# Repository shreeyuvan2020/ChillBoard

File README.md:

# The Chillboard
 ## The perfect ergonomic keyboard for chilling
 ## Features
 - Uses Xiao NRF52840 for low power usage and BLE capabilities
 - Wireless design with a 2000 mAh battery and BLE
 - CPG1350 hotswap sockets for customizabilty
 - Low profile choc switches for portability
 - Neopixel backlighting for layer switching
 - OLED panel for battery percentage
 - Tray mounted for easy assembly
 - Rotary encoder for volume control
 - PIR sensor for energy conservation
 - Ortholinear layout with a thumb cluster to reduce strain
## Reasons I built this
 - Right now, I type on a laptop keyboard and am scared that I might get carpal tunnel.
 - The switches on my other keyboard are very loud, and are not the best for me. Hotswap sockets let me customize the feel.
 - The keyboard doesn't have backlighting.
## Schematic
 For the schematic, I used hierarchial sheets to organize everything. There are 2 hierarchial sheets for each side of the pcb, and a hierarchial sheet in each one of those for the large neopixel matrix. 

 - 
 - 
 - 
## PCB
 I designed the PCB with mousebites to make the split keyboard easy to manufacture. I thought of making a reversible PCB at first, but it would be very difficult with an OLED. 
  ### Left side of the PCB 
  
  ### Full PCB
  
  ### 3D View
  
## CAD
 I designed the CAD with ease of assembly in mind. That is why I designed it with no tolerances, so that it could completely friction fit(I added screw holes for the worst case). I decided to print it with an extra fine setting on my Bambu Lab A1 Mini 3D printer, and it turned out great. 
 ### Bottom Case
 
 ### Top Plate
 
 ### Full Assembly
 
 ### Pictures of it Assembled

## My Zine

Zine is at zine.pdf too
## Assembly Instructions
 - First, obviously fabricate the PCB and solder everything.
 - Next is printing the plate and case.
 - Print with very fine settings as it friction fits, I printed with 0.08 mm High Quality @BBL on my Bambu Labs A1 Mini.
 - Be careful when removing the plate and bottom from the print bed as it could break
 - Obviously print two of each, two plates and two bottom cases
 - Then, go into the Firmware folder, open the submodule, and open Github Actions
 - Click the latest build and download the firmware artifact.
 - Then, plug in a USB cable into the Xiao and hit the reset button 2 times
 - A drive should show up, drop the first file that says settings-reset etc.
 - The drive should disappear, wait about 5 seconds and then do the same thing again
 - Then drop the file that starts with custom21
 - Now disconnect the cable, and it should show up as a BLE device
 - Connect to it then put the PCB into the bottom case
 - Then put the plate on top of it and place the keycaps on top of that to secure it.
 - You're good to go!
## Credits
 This project is inspired by the Corneucopia project by @DynamicWhiteHat.
 It used Autodesk Fusion for CAD, Kicad 10 for the PCB, and is sponsored by Hack Club Fallout! Thanks to Hack Club for sponsoring this!

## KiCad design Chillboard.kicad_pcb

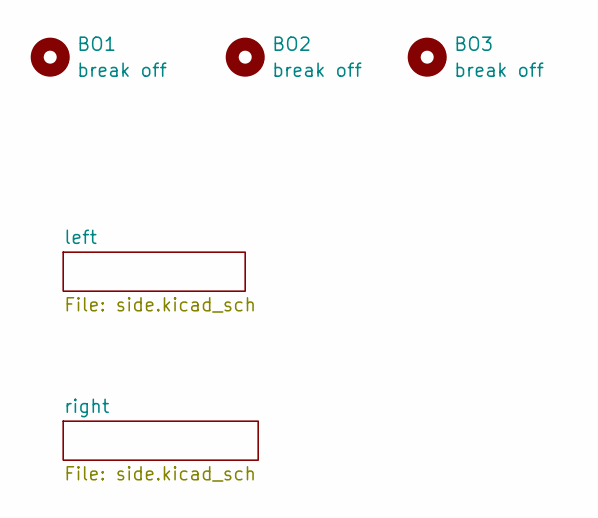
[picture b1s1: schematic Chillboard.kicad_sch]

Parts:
BO1, BO2, BO3: break off; mouse-bite-3mm-slot

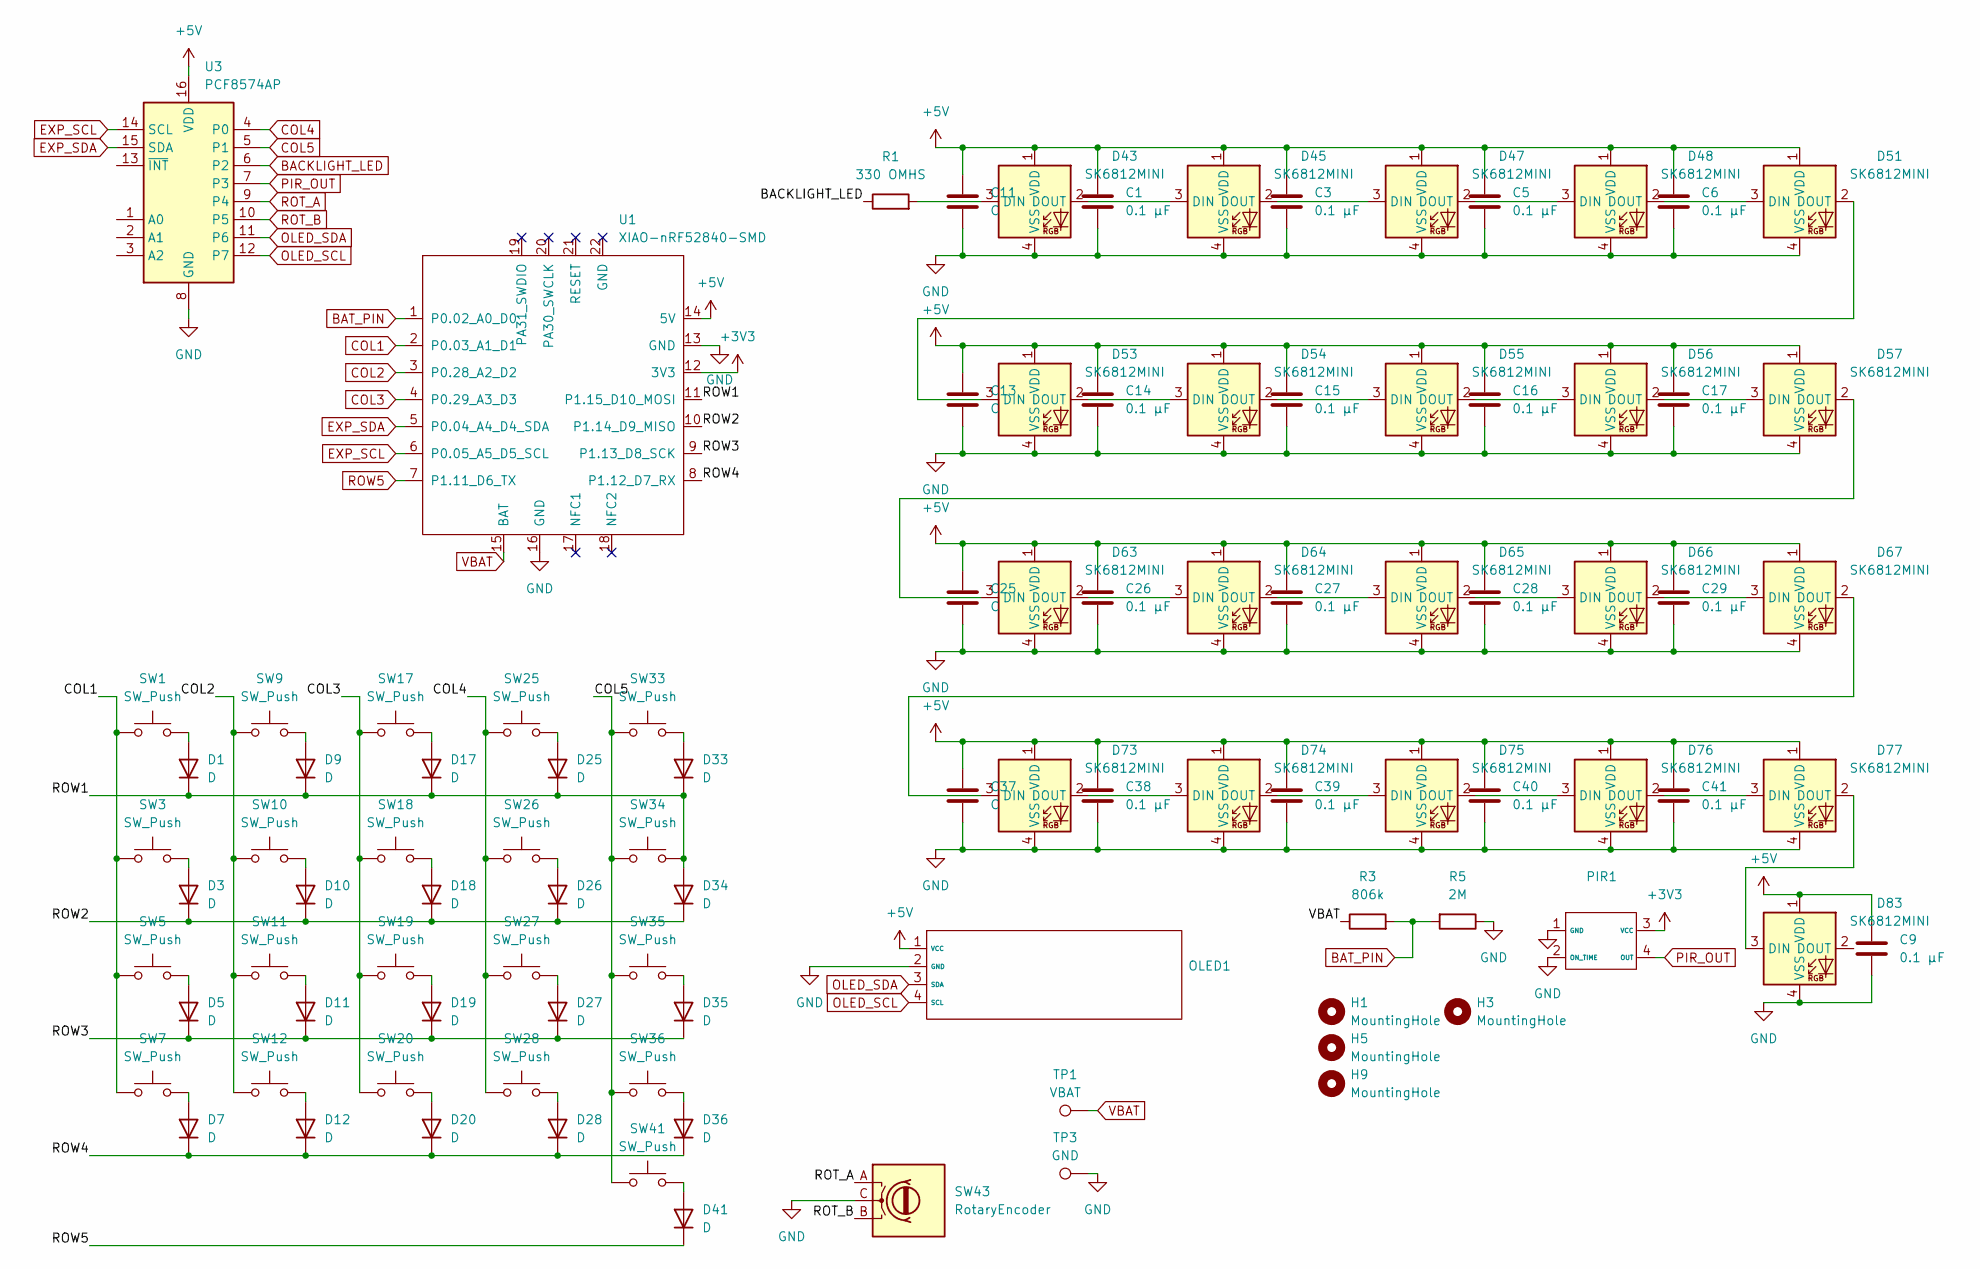
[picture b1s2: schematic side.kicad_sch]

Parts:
C1, C3, C5, C6, C9, C14, C15, C16, C17, C26, C27, C28, C29, C38, C39, C40, C41: 0.1 μF; C_0805_2012Metric
C11, C13, C25, C37: C; C_0805_2012Metric
D1, D3, D5, D7, D9, D10, D11, D12, D17, D18, D19, D20, D25, D26, D27, D28, D33, D34, D35, D36, D41: D; D_SOD-123
D43, D45, D47, D48, D51, D53, D54, D55, D56, D57, D63, D64, D65, D66, D67, D73, D74, D75, D76, D77, D83: SK6812MINI; LED_6028R
H1, H3, H5, H9: MountingHole; MountingHole_2.1mm
OLED1: SSD1306-0.91-OLED-4pin-128x32
PIR1: BS412
R1: 330 OMHS; R_Axial_DIN0207_L6.3mm_D2.5mm_P10.16mm_Horizontal
R3: 806k; R_Axial_DIN0207_L6.3mm_D2.5mm_P10.16mm_Horizontal
R5: 2M; R_Axial_DIN0207_L6.3mm_D2.5mm_P10.16mm_Horizontal
SW1, SW3, SW5, SW9, SW10, SW11, SW12, SW17, SW18, SW19, SW20, SW25, SW26, SW27, SW28, SW33, SW34, SW35, SW36, SW41: SW_Push; SW_choc_v1_HS_CPG135001S30_1u
SW7: SW_Push; SW_choc_v1_HS_CPG135001S30_1.5u
SW43: RotaryEncoder; RotaryEncoder_Alps_EC11E_Vertical_H20mm
TP1: VBAT; TestPoint_Pad_D2.0mm
TP3: GND; TestPoint_Pad_D2.0mm
U1: XIAO-nRF52840-SMD; modified-XIAO-nRF52840-SMD
U3: PCF8574AP; DIP-16_W7.62mm

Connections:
+3V3: PIR1.3 (VCC), U1.12 (3V3); also elsewhere on the board
+5V: C1.1, C3.1, C5.1, C6.1, C9.1, C11.1, C13.1, C14.1, C15.1, C16.1, C17.1, C25.1, C26.1, C27.1, C28.1, C29.1, C37.1, C38.1, C39.1, C40.1, C41.1, D43.1 (VDD), D45.1 (VDD), D47.1 (VDD), D48.1 (VDD), D51.1 (VDD), D53.1 (VDD), D54.1 (VDD), D55.1 (VDD), D56.1 (VDD), D57.1 (VDD), D63.1 (VDD), D64.1 (VDD), D65.1 (VDD), D66.1 (VDD), D67.1 (VDD), D73.1 (VDD), D74.1 (VDD), D75.1 (VDD), D76.1 (VDD), D77.1 (VDD), D83.1 (VDD), OLED1.1 (VCC), U1.14 (5V), U3.16 (VDD); also elsewhere on the board
/left/ROW1: D1.1 (K), D9.1 (K), D17.1 (K), D25.1 (K), D33.1 (K), D34.2 (A), SW34.2, U1.11 (P1.15_D10_MOSI)
/left/ROW2: D3.1 (K), D10.1 (K), D18.1 (K), D26.1 (K), D34.1 (K), U1.10 (P1.14_D9_MISO)
/left/ROW3: D5.1 (K), D11.1 (K), D19.1 (K), D27.1 (K), D35.1 (K), U1.9 (P1.13_D8_SCK)
/left/ROW4: D7.1 (K), D12.1 (K), D20.1 (K), D28.1 (K), D36.1 (K), U1.8 (P1.12_D7_RX)
BACKLIGHT_LED: R1.1, U3.6 (P2); also elsewhere on the board
BAT_PIN: R3.2, R5.2, U1.1 (P0.02_A0_D0); also elsewhere on the board
COL1: SW1.1, SW3.1, SW5.1, SW7.1, U1.2 (P0.03_A1_D1); also elsewhere on the board
COL2: SW9.1, SW10.1, SW11.1, SW12.1, U1.3 (P0.28_A2_D2); also elsewhere on the board
COL3: SW17.1, SW18.1, SW19.1, SW20.1, U1.4 (P0.29_A3_D3); also elsewhere on the board
COL4: SW25.1, SW26.1, SW27.1, SW28.1, U3.4 (P0); also elsewhere on the board
COL5: SW33.1, SW34.1, SW35.1, SW36.1, SW41.1, U3.5 (P1); also elsewhere on the board
EXP_SCL: U1.6 (P0.05_A5_D5_SCL), U3.14 (SCL); also elsewhere on the board
EXP_SDA: U1.5 (P0.04_A4_D4_SDA), U3.15 (SDA); also elsewhere on the board
GND: C1.2, C3.2, C5.2, C6.2, C9.2, C11.2, C13.2, C14.2, C15.2, C16.2, C17.2, C25.2, C26.2, C27.2, C28.2, C29.2, C37.2, C38.2, C39.2, C40.2, C41.2, D43.4 (VSS), D45.4 (VSS), D47.4 (VSS), D48.4 (VSS), D51.4 (VSS), D53.4 (VSS), D54.4 (VSS), D55.4 (VSS), D56.4 (VSS), D57.4 (VSS), D63.4 (VSS), D64.4 (VSS), D65.4 (VSS), D66.4 (VSS), D67.4 (VSS), D73.4 (VSS), D74.4 (VSS), D75.4 (VSS), D76.4 (VSS), D77.4 (VSS), D83.4 (VSS), OLED1.2 (GND), PIR1.1 (GND), PIR1.2 (ON_TIME), R5.1, SW43.C, TP3.1 (1_1), U1.13 (GND), U1.16 (GND), U3.8 (GND); also elsewhere on the board
unnamed: D1.2 (A), SW1.2
unnamed: D3.2 (A), SW3.2
unnamed: D5.2 (A), SW5.2
unnamed: D7.2 (A), SW7.2
unnamed: D9.2 (A), SW9.2
unnamed: D10.2 (A), SW10.2
unnamed: D11.2 (A), SW11.2
unnamed: D12.2 (A), SW12.2
unnamed: D17.2 (A), SW17.2
unnamed: D18.2 (A), SW18.2
unnamed: D19.2 (A), SW19.2
unnamed: D20.2 (A), SW20.2
unnamed: D25.2 (A), SW25.2
unnamed: D26.2 (A), SW26.2
unnamed: D27.2 (A), SW27.2
unnamed: D28.2 (A), SW28.2
unnamed: D33.2 (A), SW33.2
unnamed: D35.2 (A), SW35.2
unnamed: D36.2 (A), SW36.2
unnamed: D41.2 (A), SW41.2
unnamed: D43.3 (DIN), R1.2
unnamed: D43.2 (DOUT), D45.3 (DIN)
unnamed: D45.2 (DOUT), D47.3 (DIN)
unnamed: D47.2 (DOUT), D48.3 (DIN)
unnamed: D48.2 (DOUT), D51.3 (DIN)
unnamed: D51.2 (DOUT), D53.3 (DIN)
unnamed: D53.2 (DOUT), D54.3 (DIN)
unnamed: D54.2 (DOUT), D55.3 (DIN)
unnamed: D55.2 (DOUT), D56.3 (DIN)
unnamed: D56.2 (DOUT), D57.3 (DIN)
unnamed: D57.2 (DOUT), D63.3 (DIN)
unnamed: D63.2 (DOUT), D64.3 (DIN)
unnamed: D64.2 (DOUT), D65.3 (DIN)
unnamed: D65.2 (DOUT), D66.3 (DIN)
unnamed: D66.2 (DOUT), D67.3 (DIN)
unnamed: D67.2 (DOUT), D73.3 (DIN)
unnamed: D73.2 (DOUT), D74.3 (DIN)
unnamed: D74.2 (DOUT), D75.3 (DIN)
unnamed: D75.2 (DOUT), D76.3 (DIN)
unnamed: D76.2 (DOUT), D77.3 (DIN)
unnamed: D77.2 (DOUT), D83.3 (DIN)
OLED_SCL: OLED1.4 (SCL), U3.12 (P7); also elsewhere on the board
OLED_SDA: OLED1.3 (SDA), U3.11 (P6); also elsewhere on the board
PIR_OUT: PIR1.4 (OUT), U3.7 (P3); also elsewhere on the board
ROT_A: SW43.A, U3.9 (P4); also elsewhere on the board
ROT_B: SW43.B, U3.10 (P5); also elsewhere on the board
ROW5: D41.1 (K), U1.7 (P1.11_D6_TX); also elsewhere on the board
VBAT: R3.1, TP1.1 (1_1), U1.15 (BAT); also elsewhere on the board

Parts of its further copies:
C2, C4, C7, C8, C10, C20, C21, C22, C23, C32, C33, C34, C35, C44, C45, C46, C47: 0.1 μF; C_0805_2012Metric
C12, C19, C31, C43: C; C_0805_2012Metric
D2, D4, D6, D8, D13, D14, D15, D16, D21, D22, D23, D24, D29, D30, D31, D32, D37, D38, D39, D40, D42: D; D_SOD-123
D44, D46, D49, D50, D52, D58, D59, D60, D61, D62, D68, D69, D70, D71, D72, D78, D79, D80, D81, D82, D84: SK6812MINI; LED_6028R
H2, H4, H7, H11: MountingHole; MountingHole_2.1mm
R2: 330 OMHS; R_Axial_DIN0207_L6.3mm_D2.5mm_P10.16mm_Horizontal
R4: 806k; R_Axial_DIN0207_L6.3mm_D2.5mm_P10.16mm_Horizontal
R6: 2M; R_Axial_DIN0207_L6.3mm_D2.5mm_P10.16mm_Horizontal
SW2, SW4, SW6, SW13, SW14, SW15, SW16, SW21, SW22, SW23, SW24, SW29, SW30, SW31, SW32, SW37, SW38, SW39, SW40, SW42: SW_Push; SW_choc_v1_HS_CPG135001S30_1u
SW8: SW_Push; SW_choc_v1_HS_CPG135001S30_1.5u
SW44: RotaryEncoder; RotaryEncoder_Alps_EC11E_Vertical_H20mm
TP2: VBAT; TestPoint_Pad_D2.0mm
TP4: GND; TestPoint_Pad_D2.0mm
U2: XIAO-nRF52840-SMD; modified-XIAO-nRF52840-SMD
U4: PCF8574AP; DIP-16_W7.62mm

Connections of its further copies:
+3V3: U2.12 (3V3); also elsewhere on the board
+5V: C2.1, C4.1, C7.1, C8.1, C10.1, C12.1, C19.1, C20.1, C21.1, C22.1, C23.1, C31.1, C32.1, C33.1, C34.1, C35.1, C43.1, C44.1, C45.1, C46.1, C47.1, D44.1 (VDD), D46.1 (VDD), D49.1 (VDD), D50.1 (VDD), D52.1 (VDD), D58.1 (VDD), D59.1 (VDD), D60.1 (VDD), D61.1 (VDD), D62.1 (VDD), D68.1 (VDD), D69.1 (VDD), D70.1 (VDD), D71.1 (VDD), D72.1 (VDD), D78.1 (VDD), D79.1 (VDD), D80.1 (VDD), D81.1 (VDD), D82.1 (VDD), D84.1 (VDD), U2.14 (5V), U4.16 (VDD); also elsewhere on the board
/right/ROW1: D2.1 (K), D13.1 (K), D21.1 (K), D29.1 (K), D37.1 (K), D38.2 (A), SW38.2, U2.11 (P1.15_D10_MOSI)
/right/ROW2: D4.1 (K), D14.1 (K), D22.1 (K), D30.1 (K), D38.1 (K), U2.10 (P1.14_D9_MISO)
/right/ROW3: D6.1 (K), D15.1 (K), D23.1 (K), D31.1 (K), D39.1 (K), U2.9 (P1.13_D8_SCK)
/right/ROW4: D8.1 (K), D16.1 (K), D24.1 (K), D32.1 (K), D40.1 (K), U2.8 (P1.12_D7_RX)
BACKLIGHT_LED: R2.1, U4.6 (P2); also elsewhere on the board
BAT_PIN: R4.2, R6.2, U2.1 (P0.02_A0_D0); also elsewhere on the board
COL1: SW2.1, SW4.1, SW6.1, SW8.1, U2.2 (P0.03_A1_D1); also elsewhere on the board
COL2: SW13.1, SW14.1, SW15.1, SW16.1, U2.3 (P0.28_A2_D2); also elsewhere on the board
COL3: SW21.1, SW22.1, SW23.1, SW24.1, U2.4 (P0.29_A3_D3); also elsewhere on the board
COL4: SW29.1, SW30.1, SW31.1, SW32.1, U4.4 (P0); also elsewhere on the board
COL5: SW37.1, SW38.1, SW39.1, SW40.1, SW42.1, U4.5 (P1); also elsewhere on the board
EXP_SCL: U2.6 (P0.05_A5_D5_SCL), U4.14 (SCL); also elsewhere on the board
EXP_SDA: U2.5 (P0.04_A4_D4_SDA), U4.15 (SDA); also elsewhere on the board
GND: C2.2, C4.2, C7.2, C8.2, C10.2, C12.2, C19.2, C20.2, C21.2, C22.2, C23.2, C31.2, C32.2, C33.2, C34.2, C35.2, C43.2, C44.2, C45.2, C46.2, C47.2, D44.4 (VSS), D46.4 (VSS), D49.4 (VSS), D50.4 (VSS), D52.4 (VSS), D58.4 (VSS), D59.4 (VSS), D60.4 (VSS), D61.4 (VSS), D62.4 (VSS), D68.4 (VSS), D69.4 (VSS), D70.4 (VSS), D71.4 (VSS), D72.4 (VSS), D78.4 (VSS), D79.4 (VSS), D80.4 (VSS), D81.4 (VSS), D82.4 (VSS), D84.4 (VSS), R6.1, SW44.C, TP4.1 (1_1), U2.13 (GND), U2.16 (GND), U4.8 (GND); also elsewhere on the board
unnamed: D2.2 (A), SW2.2
unnamed: D4.2 (A), SW4.2
unnamed: D6.2 (A), SW6.2
unnamed: D8.2 (A), SW8.2
unnamed: D13.2 (A), SW13.2
unnamed: D14.2 (A), SW14.2
unnamed: D15.2 (A), SW15.2
unnamed: D16.2 (A), SW16.2
unnamed: D21.2 (A), SW21.2
unnamed: D22.2 (A), SW22.2
unnamed: D23.2 (A), SW23.2
unnamed: D24.2 (A), SW24.2
unnamed: D29.2 (A), SW29.2
unnamed: D30.2 (A), SW30.2
unnamed: D31.2 (A), SW31.2
unnamed: D32.2 (A), SW32.2
unnamed: D37.2 (A), SW37.2
unnamed: D39.2 (A), SW39.2
unnamed: D40.2 (A), SW40.2
unnamed: D42.2 (A), SW42.2
unnamed: D44.3 (DIN), R2.2
unnamed: D44.2 (DOUT), D46.3 (DIN)
unnamed: D46.2 (DOUT), D49.3 (DIN)
unnamed: D49.2 (DOUT), D50.3 (DIN)
unnamed: D50.2 (DOUT), D52.3 (DIN)
unnamed: D52.2 (DOUT), D58.3 (DIN)
unnamed: D58.2 (DOUT), D59.3 (DIN)
unnamed: D59.2 (DOUT), D60.3 (DIN)
unnamed: D60.2 (DOUT), D61.3 (DIN)
unnamed: D61.2 (DOUT), D62.3 (DIN)
unnamed: D62.2 (DOUT), D68.3 (DIN)
unnamed: D68.2 (DOUT), D69.3 (DIN)
unnamed: D69.2 (DOUT), D70.3 (DIN)
unnamed: D70.2 (DOUT), D71.3 (DIN)
unnamed: D71.2 (DOUT), D72.3 (DIN)
unnamed: D72.2 (DOUT), D78.3 (DIN)
unnamed: D78.2 (DOUT), D79.3 (DIN)
unnamed: D79.2 (DOUT), D80.3 (DIN)
unnamed: D80.2 (DOUT), D81.3 (DIN)
unnamed: D81.2 (DOUT), D82.3 (DIN)
unnamed: D82.2 (DOUT), D84.3 (DIN)
OLED_SCL: U4.12 (P7); also elsewhere on the board
OLED_SDA: U4.11 (P6); also elsewhere on the board
PIR_OUT: U4.7 (P3); also elsewhere on the board
ROT_A: SW44.A, U4.9 (P4); also elsewhere on the board
ROT_B: SW44.B, U4.10 (P5); also elsewhere on the board
ROW5: D42.1 (K), U2.7 (P1.11_D6_TX); also elsewhere on the board
VBAT: R4.1, TP2.1 (1_1), U2.15 (BAT); also elsewhere on the board

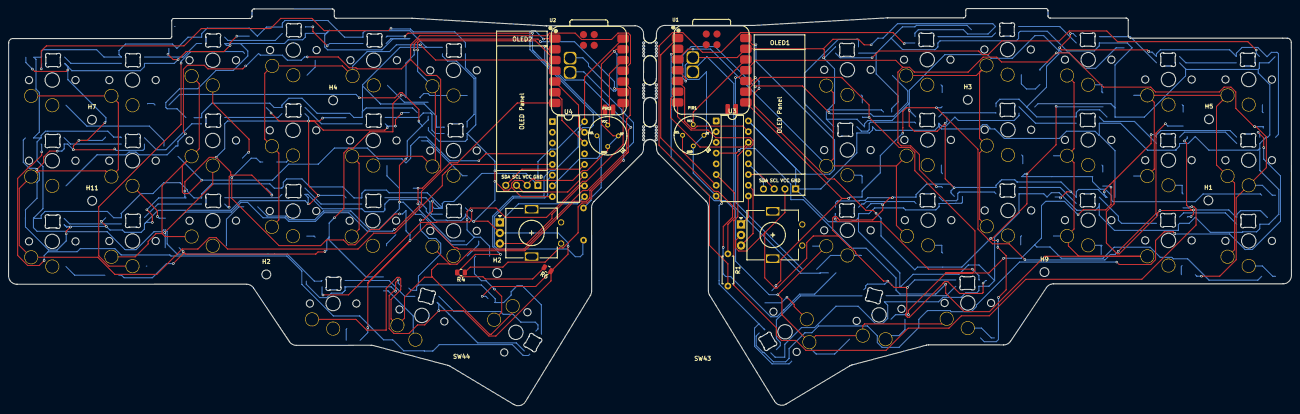
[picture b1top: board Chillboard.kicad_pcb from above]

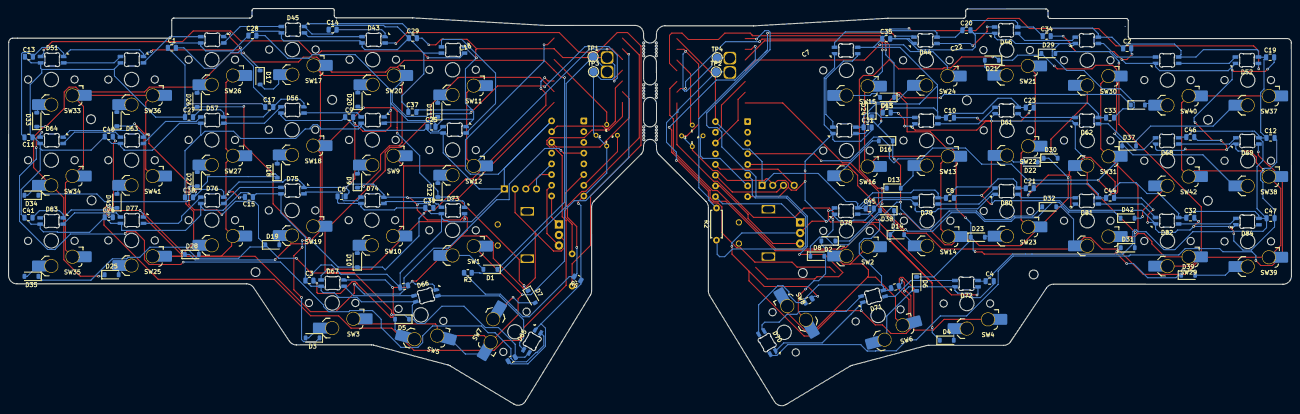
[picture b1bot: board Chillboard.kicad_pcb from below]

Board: 2 copper layers, 303.7 x 94.0 mm, 200 parts (175 on the bottom side), 109 nets.

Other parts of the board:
H2#2: MountingHole; MountingHole_2.1mm
OLED2: SSD1306-0.91-OLED-4pin-128x32
PIR2: BS412

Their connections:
+3V3: PIR2.3 (VCC); also elsewhere on the board
+5V: OLED2.1 (VCC); also elsewhere on the board
GND: OLED2.2 (GND), PIR2.1 (GND), PIR2.2 (ON_TIME); also elsewhere on the board
OLED_SCL: OLED2.4 (SCL); also elsewhere on the board
OLED_SDA: OLED2.3 (SDA); also elsewhere on the board
PIR_OUT: PIR2.4 (OUT); also elsewhere on the board

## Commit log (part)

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2026-05-01 deleted stuff
2026-05-10 done
2026-05-31 fdhshfadshkfdsahhfadshjkfds
2026-06-07 readme stuff
2026-06-07 ahjkhdfhjkusdhfhj
2026-06-09 Reorganize repository: clean .gitignore and move libraries/3D-models/exports to organized folders
    - Added comprehensive .gitignore for KiCad generated files, caches, macOS artifacts, and build outputs
    - Moved 3D model files (*.step, *.wrl) to 3D-Models/
    - Moved symbol libraries to libraries/symbols/
    - Moved footprint libraries to libraries/footprints/custom/ and libraries/footprints/panelization/
    - Moved exports (DXF, SVG, Gerbers.zip) to generated-exports/
    - Removed incorrectly tracked files: lock files, cache files, backup files, generated renders
2026-06-09 Reorganize into main project categories: PCB, CAD, Manufacturing, Firmware, Documentation
    - PCB/: KiCad project files (schematics, board layout) + symbol/footprint libraries
    - CAD/: 3D models (.step, .wrl) + design exports (DXF, SVG)
    - Manufacturing/: Gerber files + project backups
    - Firmware/: ZMK keyboard firmware configuration
    - Documentation/: Project images and assets
    This hierarchical structure improves project navigation and clarity.
2026-06-09 Move assets folder to root, remove Documentation directory
    - assets/ now at root level for easier access
    - Removed nested Documentation/ directory structure
2026-06-09 Track assets folder in version control
    - Updated .gitignore to allow assets/ directory despite *.png pattern
    - Added all project images to version control
2026-06-10 add bom
2026-06-10 Add Firmware/zmk-config as git submodule
2026-06-10 add zine
2026-06-10 change readme
    Added reasons for building the keyboard to README.
2026-06-10 add fusion files
2026-06-10 fdgagfsdg
2026-06-10 add step
2026-06-10 organize into cad folder
2026-06-10 organize cad folder
2026-06-10 make it to bom.csv instead of weird name
2026-06-10 write assembly
2026-06-10 add assembly instructions
2026-06-10 gerbers.zip
2026-06-10 Rename MITO-2.png to zine.png
2026-06-10 add zine to readme
2026-06-11 make bom.csv optimized
2026-06-11 make it coolio
2026-06-11 add sockets
2026-06-12 change key switches
2026-06-12 change to remove customs,. new total
2026-06-12 make it cool
2026-06-12 change for ez description ig
2026-06-12 Rename MITO.pdf to zine.pdf
2026-06-12 change to new file path
    Updated zine image reference to point to PDF file.
2026-06-12 change to real filepath
2026-06-12 change to real????? filepath once again
    Updated zine link to use relative path.
2026-06-12 uhh change cuz markdown been weird
2026-06-12 make assembly clear
2026-06-25 new zine
2026-06-25 Rename MITO-2.pdf to zine.pdf
2026-06-25 add built
    Added pictures of the assembled project to the README.
2026-06-25 add pics
    Replaced old assembly images with new HEIC format images.
